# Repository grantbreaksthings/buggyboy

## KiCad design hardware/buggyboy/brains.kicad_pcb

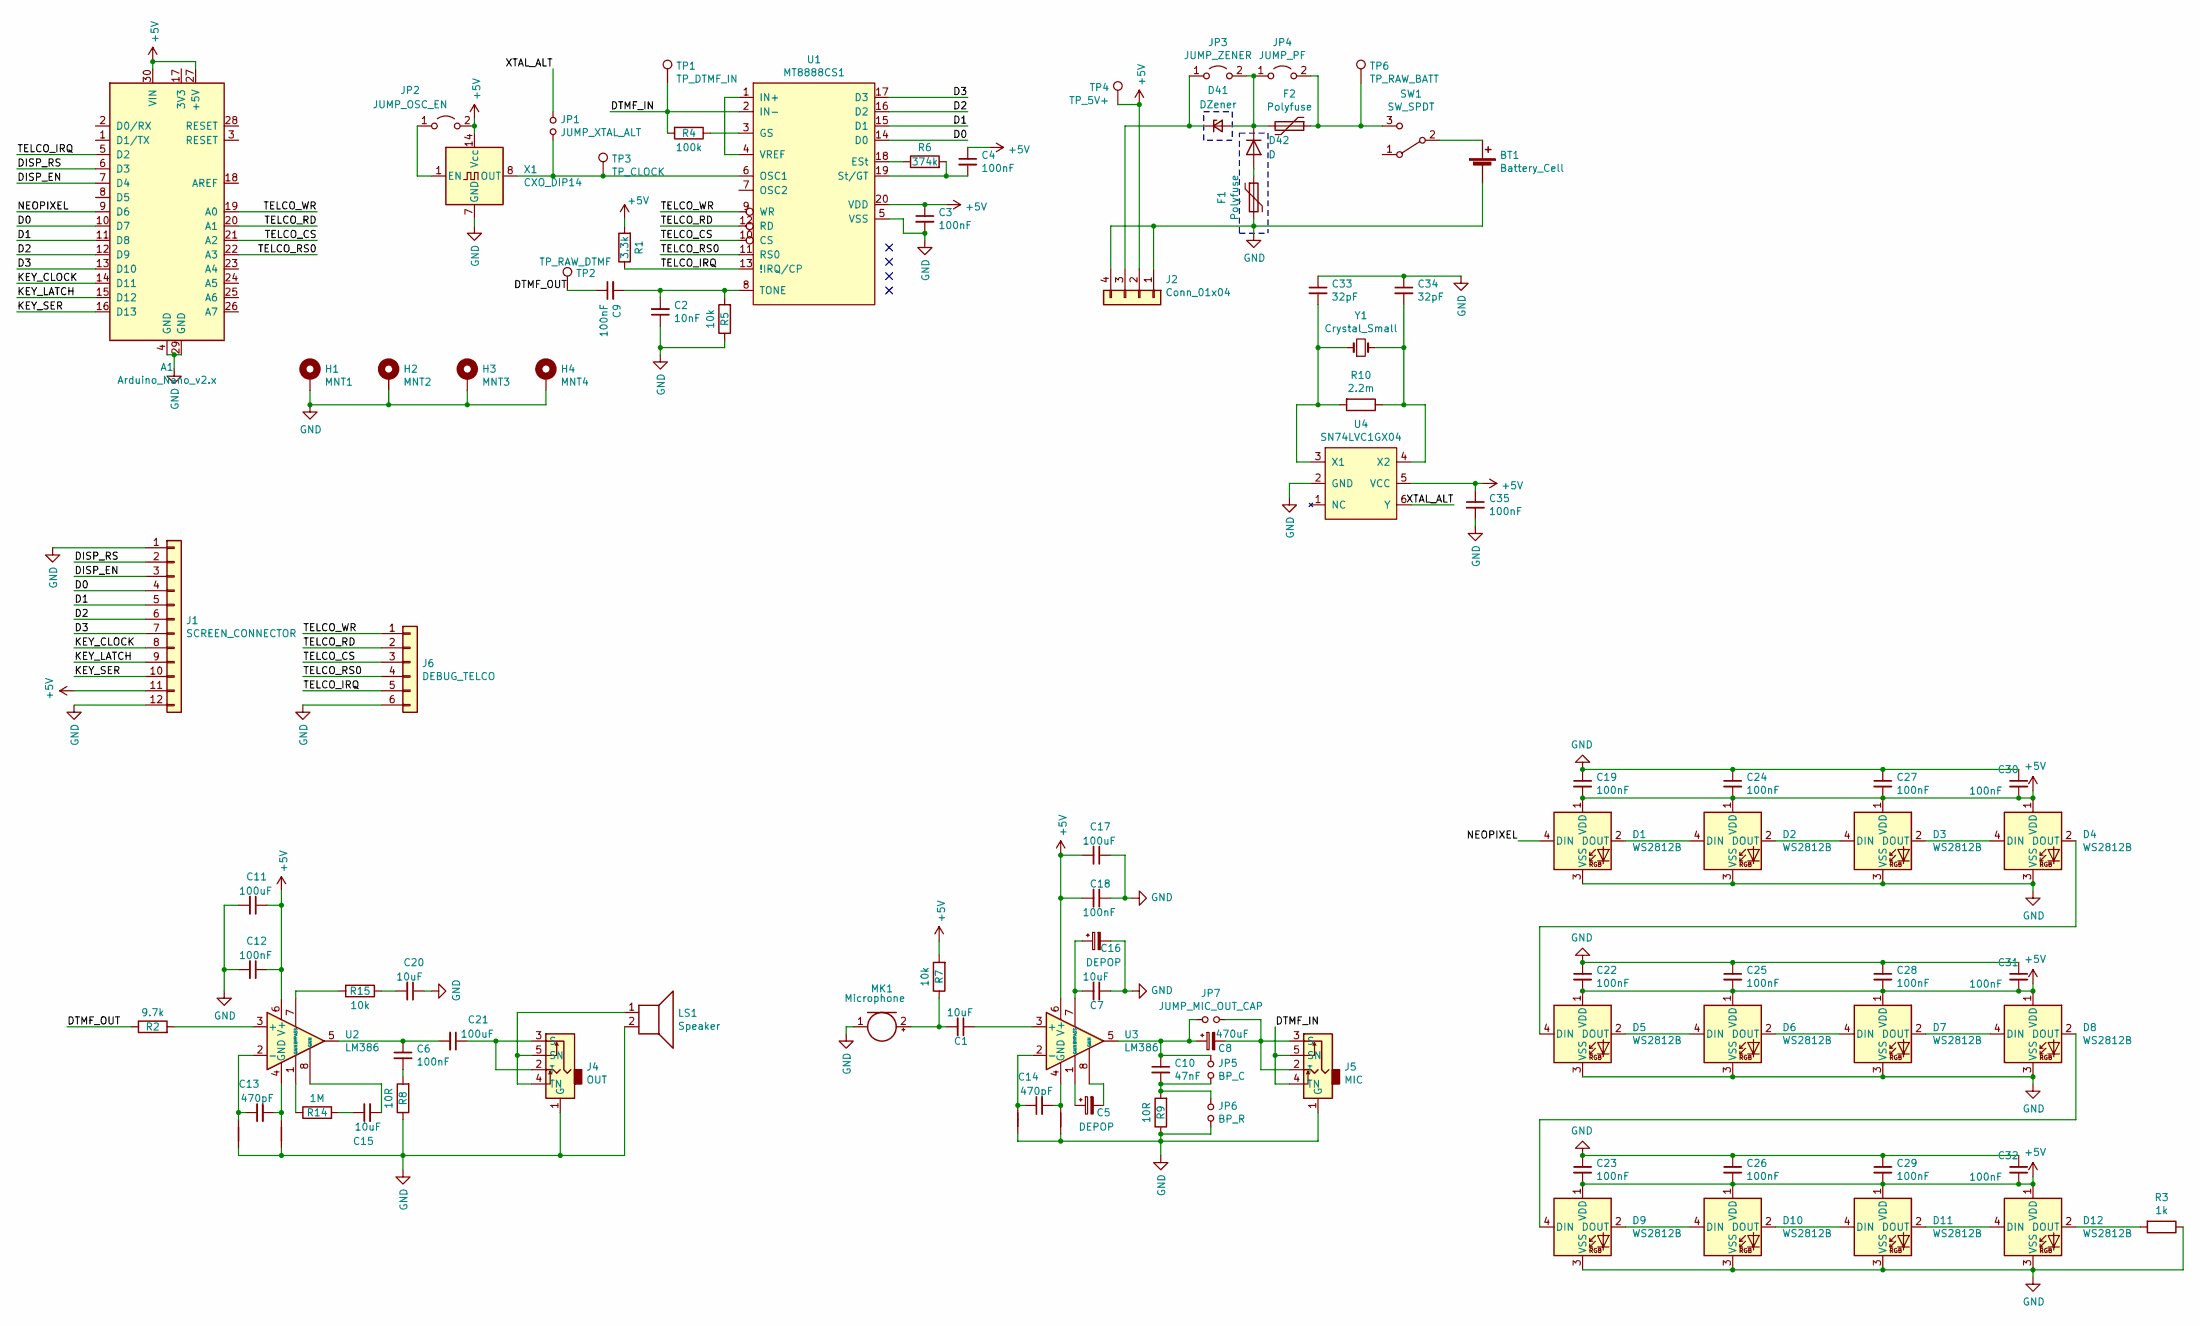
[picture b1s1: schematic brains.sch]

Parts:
A1: Arduino_Nano_v2.x; Arduino_Nano
BT1: Battery_Cell; BatteryHolder_BC2AAPC
C1, C7, C15, C20: 10uF; C_0805_2012Metric_Pad1.18x1.45mm_HandSolder
C2: 10nF; C_0805_2012Metric_Pad1.18x1.45mm_HandSolder
C3, C4, C6, C9, C12, C18, C19, C22, C23, C24, C25, C26, C27, C28, C29, C30, C31, C32, C35: 100nF; C_0603_1608Metric_Pad1.08x0.95mm_HandSolder
C5, C16: DEPOP; CP_Radial_D8.0mm_P3.80mm
C8: 470uF; CP_Radial_D8.0mm_P3.80mm
C10: 47nF; C_0603_1608Metric_Pad1.08x0.95mm_HandSolder
C11, C17, C21: 100uF; C_1206_3216Metric_Pad1.33x1.80mm_HandSolder
C13, C14: 470pF; C_0805_2012Metric_Pad1.18x1.45mm_HandSolder
C33, C34: 32pF; C_0402_1005Metric_Pad0.74x0.62mm_HandSolder
D1, D2, D3, D4, D5, D6, D7, D8, D9, D10, D11, D12: WS2812B; LED_WS2812B_PLCC4_5.0x5.0mm_P3.2mm
D41: DZener; D_SMB_Handsoldering
D42: D; D_SMA_Handsoldering
F1, F2: Polyfuse; Fuse_Littelfuse_395Series
H1: MNT1; MountingHole_4.3mm_M4_Pad_Via
H2: MNT2; MountingHole_4.3mm_M4_Pad_Via
H3: MNT3; MountingHole_4.3mm_M4_Pad_Via
H4: MNT4; MountingHole_4.3mm_M4_Pad_Via
J1: SCREEN_CONNECTOR; PinHeader_1x12_P2.54mm_Vertical
J2: Conn_01x04; MT3608_MODULE
J4: OUT; CUI_SJ1-3545N
J5: MIC; CUI_SJ1-3545N
J6: DEBUG_TELCO; PinHeader_1x06_P2.54mm_Vertical
JP1: JUMP_XTAL_ALT; SolderJumper-2_P1.3mm_Open_RoundedPad1.0x1.5mm
JP2: JUMP_OSC_EN; SolderJumper-2_P1.3mm_Open_RoundedPad1.0x1.5mm
JP3: JUMP_ZENER; SolderJumper-2_P1.3mm_Open_RoundedPad1.0x1.5mm
JP4: JUMP_PF; SolderJumper-2_P1.3mm_Open_RoundedPad1.0x1.5mm
JP5: BP_C; SolderJumper-2_P1.3mm_Open_RoundedPad1.0x1.5mm
JP6: BP_R; SolderJumper-2_P1.3mm_Open_RoundedPad1.0x1.5mm
JP7: JUMP_MIC_OUT_CAP; SolderJumper-2_P1.3mm_Open_RoundedPad1.0x1.5mm
LS1: Speaker; PinSocket_1x02_P2.54mm_Vertical
MK1: Microphone; PinSocket_1x02_P2.54mm_Vertical
NT1, NT2, NT3, NT4: Net-Tie_2; NetTie-2_SMD_Pad0.5mm
R1: 3.3k; R_0805_2012Metric_Pad1.20x1.40mm_HandSolder
R2: 9.7k; R_0805_2012Metric_Pad1.20x1.40mm_HandSolder
R3: 1k; R_0805_2012Metric_Pad1.20x1.40mm_HandSolder
R4: 100k; R_0805_2012Metric_Pad1.20x1.40mm_HandSolder
R5, R7, R15: 10k; R_0805_2012Metric_Pad1.20x1.40mm_HandSolder
R6: 374k; R_0805_2012Metric_Pad1.20x1.40mm_HandSolder
R8, R9: 10R; R_0805_2012Metric_Pad1.20x1.40mm_HandSolder
R10: 2.2m; R_0805_2012Metric_Pad1.20x1.40mm_HandSolder
R14: 1M; R_0805_2012Metric_Pad1.20x1.40mm_HandSolder
SW1: SW_SPDT; SW_E-Switch_EG1224_SPDT_Angled
TP1: TP_DTMF_IN; TestPoint_Pad_D2.5mm
TP2: TP_RAW_DTMF; TestPoint_Pad_D2.5mm
TP3: TP_CLOCK; TestPoint_Pad_D2.5mm
TP4: TP_5V+; TestPoint_Pad_D2.5mm
TP6: TP_RAW_BATT; TestPoint_Pad_D2.5mm
U1: MT8888CS1; SOIC-20W_7.5x12.8mm_P1.27mm
U2, U3: LM386; DIP-8_W7.62mm_LongPads
U4: SN74LVC1GX04; SOT-563
X1: CXO_DIP14; Oscillator_DIP-14
Y1: Crystal_Small; Crystal_HC49-U_Vertical

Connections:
+5V: A1.27 (+5V), A1.30 (VIN), C3.1, C4.1, C11.1, C12.1, C17.2, C18.2, C19.2, C22.2, C23.2, C24.2, C25.2, C26.2, C27.2, C28.2, C29.2, C30.2, C31.2, C32.2, C35.1, D1.1 (VDD), D2.1 (VDD), D3.1 (VDD), D4.1 (VDD), D5.1 (VDD), D6.1 (VDD), D7.1 (VDD), D8.1 (VDD), D9.1 (VDD), D10.1 (VDD), D11.1 (VDD), D12.1 (VDD), J1.11, J2.2, JP2.2 (B), R1.2, R7.2, TP4.1, U1.20 (VDD), U2.6 (V+), U3.6 (V+), U4.5 (VCC), X1.14 (Vcc)
/D0: A1.10 (D7), J1.4, U1.14 (D0)
/D1: A1.11 (D8), J1.5, U1.15 (D1)
/D2: A1.12 (D9), J1.6, U1.16 (D2)
/D3: A1.13 (D10), J1.7, U1.17 (D3)
/DISP_EN: A1.7 (D4), J1.3
/DISP_RS: A1.6 (D3), J1.2
/DTMF_IN: J5.4 (TN), J5.5 (SN), R4.2, TP1.1, U1.2 (IN-)
/DTMF_OUT: C9.1, R2.1, TP2.1
/KEY_CLOCK: A1.14 (D11), J1.8
/KEY_LATCH: A1.15 (D12), J1.9
/KEY_SER: A1.16 (D13), J1.10
/NEOPIXEL: A1.9 (D6), D1.4 (DIN)
/TELCO_CS: A1.21 (A2), J6.3, U1.10 (CS)
/TELCO_IRQ: A1.5 (D2), J6.5, R1.1, U1.13 (!IRQ/CP)
/TELCO_RD: A1.20 (A1), J6.2, U1.12 (RD)
/TELCO_RS0: A1.22 (A3), J6.4, U1.11 (RS0)
/TELCO_WR: A1.19 (A0), J6.1, U1.9 (WR)
/XTAL_ALT: JP1.1, U4.6 (Y)
GND: A1.4 (GND), A1.29 (GND), BT1.2 (-), C2.1, C3.2, C7.1, C11.2, C12.2, C16.2, C17.1, C18.1, C19.1, C20.1, C22.1, C23.1, C24.1, C25.1, C26.1, C27.1, C28.1, C29.1, C30.1, C31.1, C32.1, C33.1, C34.1, C35.2, D1.3 (VSS), D2.3 (VSS), D3.3 (VSS), D4.3 (VSS), D5.3 (VSS), D6.3 (VSS), D7.3 (VSS), D8.3 (VSS), D9.3 (VSS), D10.3 (VSS), D11.3 (VSS), D12.3 (VSS), F1.2, H1.1, H2.1, H3.1, H4.1, J1.1, J1.12, J2.1, J2.4, J4.1 (G), J5.1 (G), J6.6, JP6.2, LS1.2, MK1.1 (-), NT1.2, NT2.2, NT3.2, NT4.2, R3.1, R5.1, R8.1, R9.1, U1.5 (VSS), U4.2 (GND), X1.7 (GND)
unnamed: BT1.1 (+), SW1.2 (B)
unnamed: C1.1, U3.3 (+)
unnamed: C1.2, MK1.2 (+), R7.1
unnamed: C2.2, C9.2, R5.2, U1.8 (TONE)
unnamed: C4.2, R6.2, U1.19 (St/GT)
unnamed: C5.1, U3.1 (GAIN)
unnamed: C5.2, U3.8 (GAIN)
unnamed: C6.2, R8.2
unnamed: C8.2, J5.2 (T), J5.3 (S), JP7.2
unnamed: C8.1, C10.1, JP5.1, JP7.1, U3.5
unnamed: C10.2, JP5.2, JP6.1, R9.2
unnamed: C13.1, NT1.1, U2.2 (-)
unnamed: C13.2, NT2.1, U2.4 (GND)
unnamed: C14.1, NT3.1, U3.2 (-)
unnamed: C14.2, NT4.1, U3.4 (GND)
unnamed: C15.1, R14.2
unnamed: C15.2, U2.8 (GAIN)
unnamed: C7.2, C16.1, U3.7 (BYPASS)
unnamed: C20.2, R15.1
unnamed: C21.1, J4.2 (T), J4.3 (S)
unnamed: C6.1, C21.2, U2.5
unnamed: C33.2, R10.2, U4.3 (X1), Y1.1
unnamed: C34.2, R10.1, U4.4 (X2), Y1.2
unnamed: D1.2 (DOUT), D2.4 (DIN)
unnamed: D2.2 (DOUT), D3.4 (DIN)
unnamed: D3.2 (DOUT), D4.4 (DIN)
unnamed: D4.2 (DOUT), D5.4 (DIN)
unnamed: D5.2 (DOUT), D6.4 (DIN)
unnamed: D6.2 (DOUT), D7.4 (DIN)
unnamed: D7.2 (DOUT), D8.4 (DIN)
unnamed: D8.2 (DOUT), D9.4 (DIN)
unnamed: D10.2 (DOUT), D11.4 (DIN)
unnamed: D9.2 (DOUT), D10.4 (DIN)
unnamed: D11.2 (DOUT), D12.4 (DIN)
unnamed: D12.2 (DOUT), R3.2
unnamed: D41.1 (K), J2.3, JP3.1 (A)
unnamed: D41.2 (A), D42.1 (K), F2.2, JP3.2 (B), JP4.1 (A)
unnamed: D42.2 (A), F1.1
unnamed: F2.1, JP4.2 (B), SW1.3 (C), TP6.1
unnamed: J4.4 (TN), J4.5 (SN), LS1.1
unnamed: JP1.2, TP3.1, U1.6 (OSC1), X1.8 (OUT)
unnamed: JP2.1 (A), X1.1 (EN)
unnamed: R2.2, U2.3 (+)
unnamed: R4.1, U1.3 (GS)
unnamed: R6.1, U1.18 (ESt)
unnamed: R14.1, U2.1 (GAIN)
unnamed: R15.2, U2.7 (BYPASS)
unnamed: U1.1 (IN+), U1.4 (VREF)

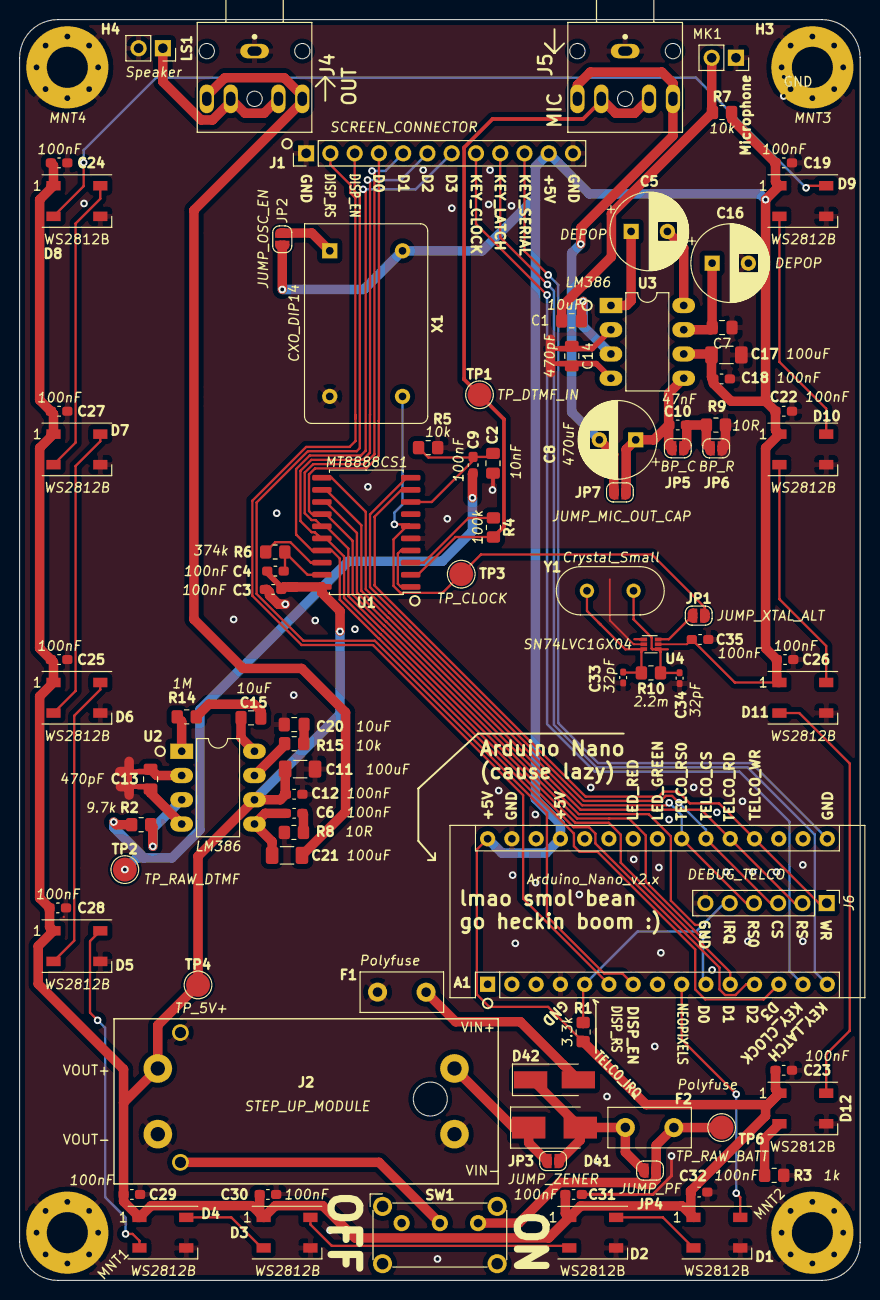
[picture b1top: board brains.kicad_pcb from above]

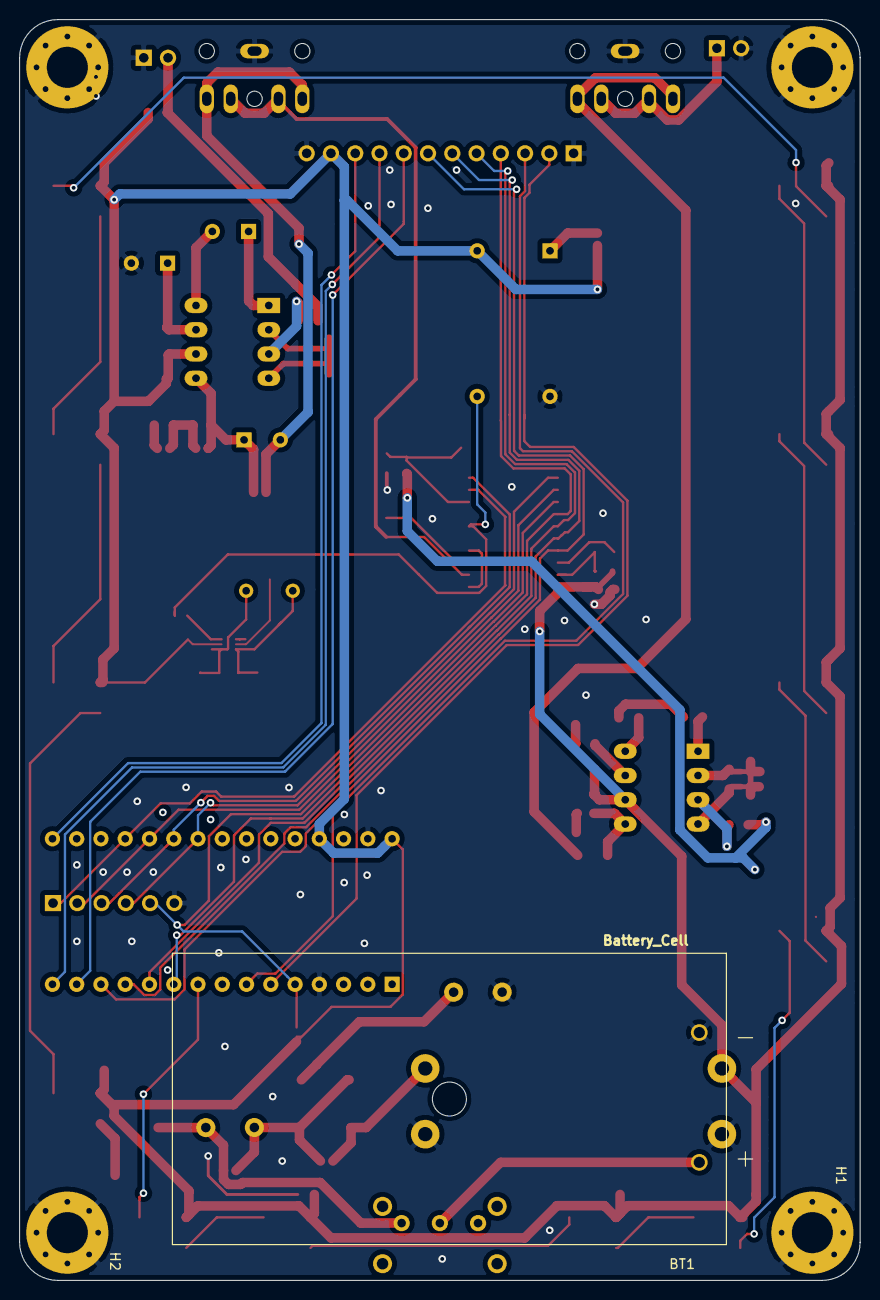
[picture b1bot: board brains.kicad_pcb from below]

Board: 2 copper layers, 88.0 x 132.0 mm, 99 parts (3 on the bottom side), 68 nets.

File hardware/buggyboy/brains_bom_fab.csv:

Designator,Package,Quantity,Designation,LCSC Part Number
"C22,C3,C4,C6,C9,C12,C18,C19,C23,C24,C25,C26,C27,C28,C29,C30,C31,C32,C35",C_0603_1608Metric_Pad1.08x0.95mm_HandSolder,19,100nF,C14663
"D9,D2,D6,D10,D3,D7,D11,D4,D8,D12,D1,D5",LED_WS2812B_PLCC4_5.0x5.0mm_P3.2mm,12,WS2812B,C2761795
"C1,C15,C20, C7",C_0805_2012Metric_Pad1.18x1.45mm_HandSolder,3,10uF,C15850
C10,C_0603_1608Metric_Pad1.08x0.95mm_HandSolder,1,47nF,C1622
"C11,C17,C21",C_1206_3216Metric_Pad1.33x1.80mm_HandSolder,3,100uF,C15008
"C13,C14",C_0805_2012Metric_Pad1.18x1.45mm_HandSolder,2,470pF,C1743
D42,D_SMA_Handsoldering,1,D,C95872
R1,R_0805_2012Metric_Pad1.20x1.40mm_HandSolder,1,3.3k,C26010
R2,R_0805_2012Metric_Pad1.20x1.40mm_HandSolder,1,9.7k,C17414
R4,R_0805_2012Metric_Pad1.20x1.40mm_HandSolder,1,100k,C149504
"R5,R7,R15",R_0805_2012Metric_Pad1.20x1.40mm_HandSolder,3,10k,C17414
R6,R_0805_2012Metric_Pad1.20x1.40mm_HandSolder,1,374k,C17649
"R8,R9",R_0805_2012Metric_Pad1.20x1.40mm_HandSolder,2,10R,C17415
R14,R_0805_2012Metric_Pad1.20x1.40mm_HandSolder,1,1M,C17514
R3,R_0805_2012Metric_Pad1.20x1.40mm_HandSolder,1,1k,C17513
"C33,C34",C_0402_Metric_Pad1.08x0.95mm_HandSolder,2,32pF,C1570
R10,R_0805_2012Metric_Pad1.20x1.40mm_HandSolder,1,2.2m,C26113

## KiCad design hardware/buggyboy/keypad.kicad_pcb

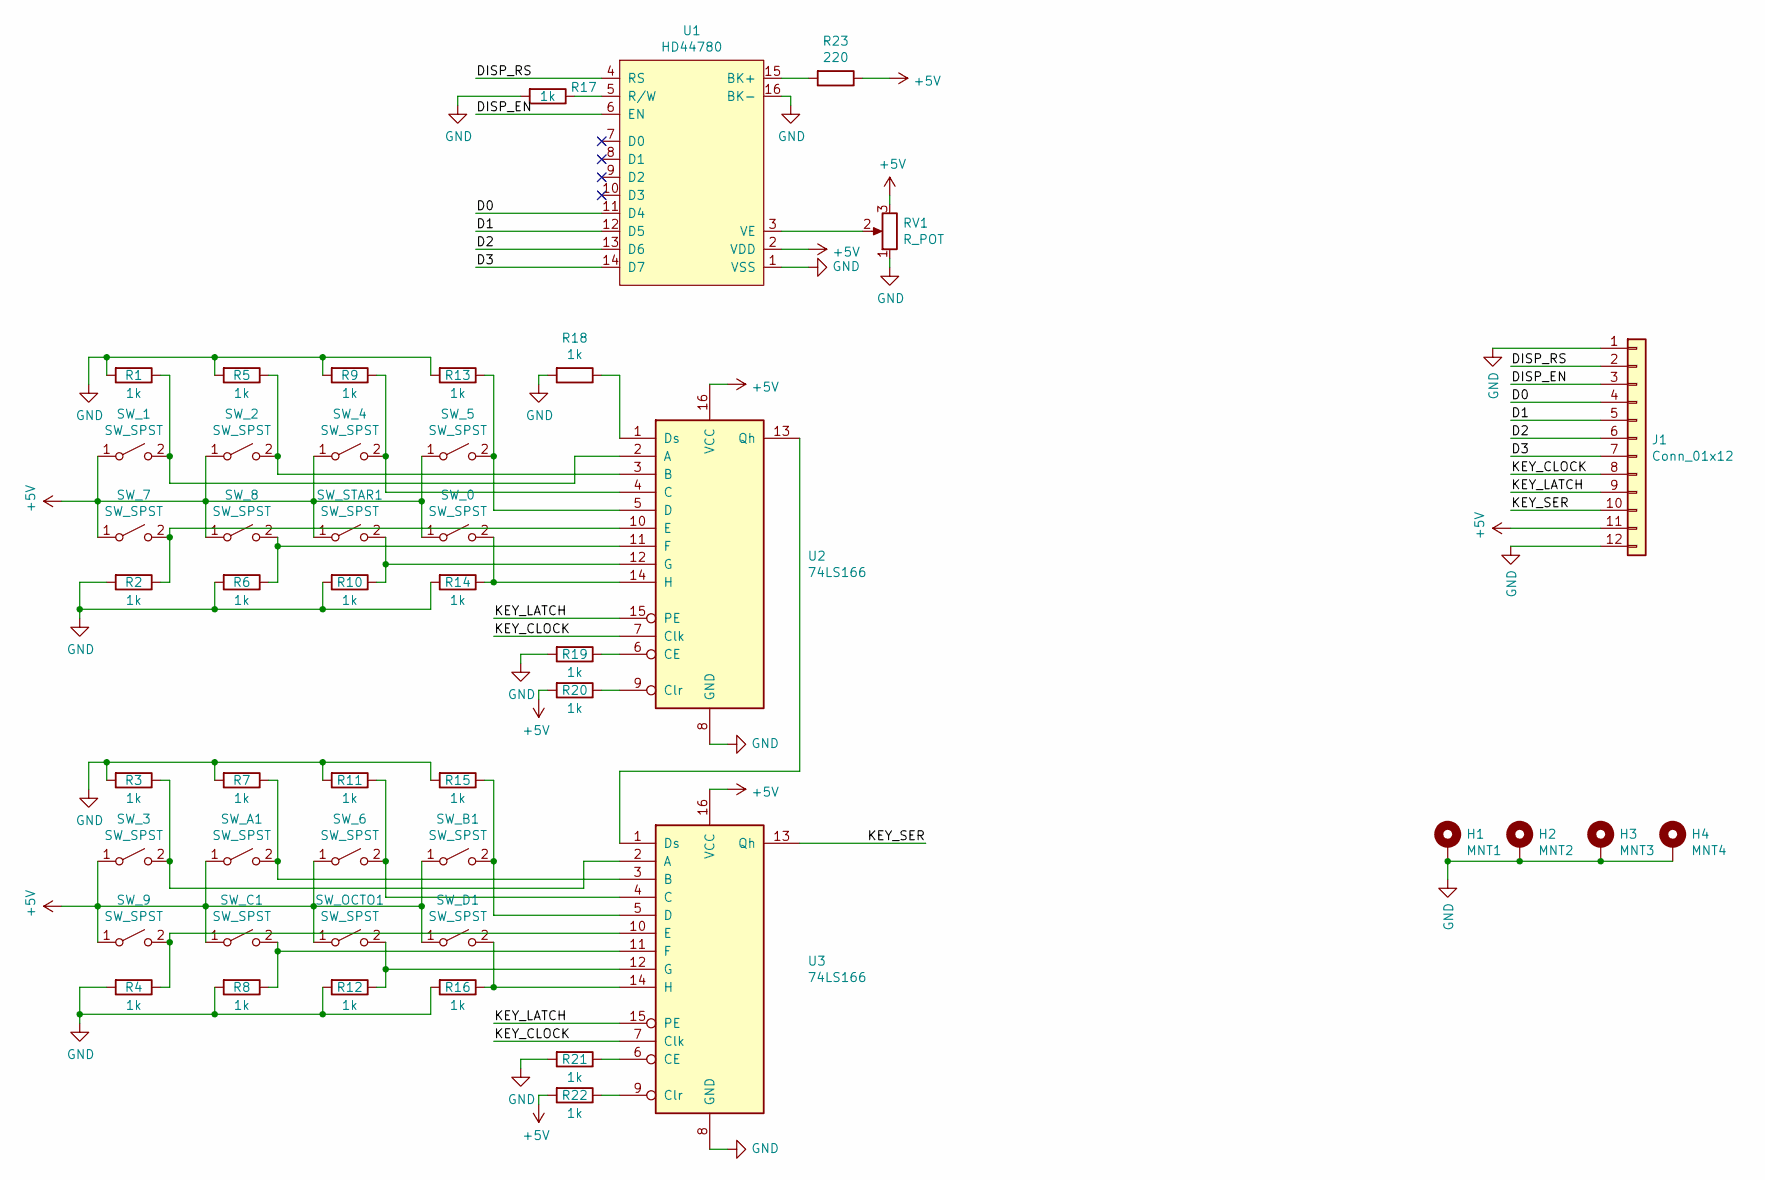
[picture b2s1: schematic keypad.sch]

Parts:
H1: MNT1; MountingHole_4.3mm_M4_Pad_Via
H2: MNT2; MountingHole_4.3mm_M4_Pad_Via
H3: MNT3; MountingHole_4.3mm_M4_Pad_Via
H4: MNT4; MountingHole_4.3mm_M4_Pad_Via
J1: Conn_01x12; PinHeader_1x12_P2.54mm_Vertical
R1, R2, R3, R4, R5, R6, R7, R8, R9, R10, R11, R12, R13, R14, R15, R16, R17, R18, R19, R20, R21, R22: 1k; R_0603_1608Metric_Pad0.98x0.95mm_HandSolder
R23: 220; R_0603_1608Metric_Pad0.98x0.95mm_HandSolder
RV1: R_POT; TRIM_3313J-1-103E
SW_0, SW_1, SW_2, SW_3, SW_4, SW_5, SW_6, SW_7, SW_8, SW_9: SW_SPST; SW_Cherry_MX_1.00u_PCB
SW_A1: SW_SPST; SW_Cherry_MX_1.00u_PCB
SW_B1: SW_SPST; SW_Cherry_MX_1.00u_PCB
SW_C1: SW_SPST; SW_Cherry_MX_1.00u_PCB
SW_D1: SW_SPST; SW_Cherry_MX_1.00u_PCB
SW_OCTO1: SW_SPST; SW_Cherry_MX_1.00u_PCB
SW_STAR1: SW_SPST; SW_Cherry_MX_1.00u_PCB
U1: HD44780; WC1602A
U2, U3: 74LS166; DIP-16_W7.62mm_LongPads

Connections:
+5V: J1.11, R20.2, R22.2, R23.1, RV1.3, SW_0.1 (A), SW_1.1 (A), SW_2.1 (A), SW_3.1 (A), SW_4.1 (A), SW_5.1 (A), SW_6.1 (A), SW_7.1 (A), SW_8.1 (A), SW_9.1 (A), SW_A1.1 (A), SW_B1.1 (A), SW_C1.1 (A), SW_D1.1 (A), SW_OCTO1.1 (A), SW_STAR1.1 (A), U1.2 (VDD), U2.16 (VCC), U3.16 (VCC)
/D0: J1.4, U1.11 (D4)
/D1: J1.5, U1.12 (D5)
/D2: J1.6, U1.13 (D6)
/D3: J1.7, U1.14 (D7)
/DISP_EN: J1.3, U1.6 (EN)
/DISP_RS: J1.2, U1.4 (RS)
/KEY_CLOCK: J1.8, U2.7 (Clk), U3.7 (Clk)
/KEY_LATCH: J1.9, U2.15 (PE), U3.15 (PE)
/KEY_SER: J1.10, U3.13 (Qh)
GND: H1.1, H2.1, H3.1, H4.1, J1.1, J1.12, R1.2, R2.2, R3.2, R4.2, R5.2, R6.2, R7.2, R8.2, R9.2, R10.2, R11.2, R12.2, R13.2, R14.2, R15.2, R16.2, R17.2, R18.2, R19.2, R21.2, RV1.1, U1.1 (VSS), U1.16 (BK-), U2.8 (GND), U3.8 (GND)
unnamed: R1.1, SW_1.2 (B), U2.2 (A)
unnamed: R2.1, SW_7.2 (B), U2.10 (E)
unnamed: R3.1, SW_3.2 (B), U3.2 (A)
unnamed: R4.1, SW_9.2 (B), U3.10 (E)
unnamed: R5.1, SW_2.2 (B), U2.3 (B)
unnamed: R6.1, SW_8.2 (B), U2.11 (F)
unnamed: R7.1, SW_A1.2 (B), U3.3 (B)
unnamed: R8.1, SW_C1.2 (B), U3.11 (F)
unnamed: R9.1, SW_4.2 (B), U2.4 (C)
unnamed: R10.1, SW_STAR1.2 (B), U2.12 (G)
unnamed: R11.1, SW_6.2 (B), U3.4 (C)
unnamed: R12.1, SW_OCTO1.2 (B), U3.12 (G)
unnamed: R13.1, SW_5.2 (B), U2.5 (D)
unnamed: R14.1, SW_0.2 (B), U2.14 (H)
unnamed: R15.1, SW_B1.2 (B), U3.5 (D)
unnamed: R16.1, SW_D1.2 (B), U3.14 (H)
unnamed: R17.1, U1.5 (R/W)
unnamed: R18.1, U2.1 (Ds)
unnamed: R19.1, U2.6 (CE)
unnamed: R20.1, U2.9 (Clr)
unnamed: R21.1, U3.6 (CE)
unnamed: R22.1, U3.9 (Clr)
unnamed: R23.2, U1.15 (BK+)
unnamed: RV1.2, U1.3 (VE)
unnamed: U2.13 (Qh), U3.1 (Ds)

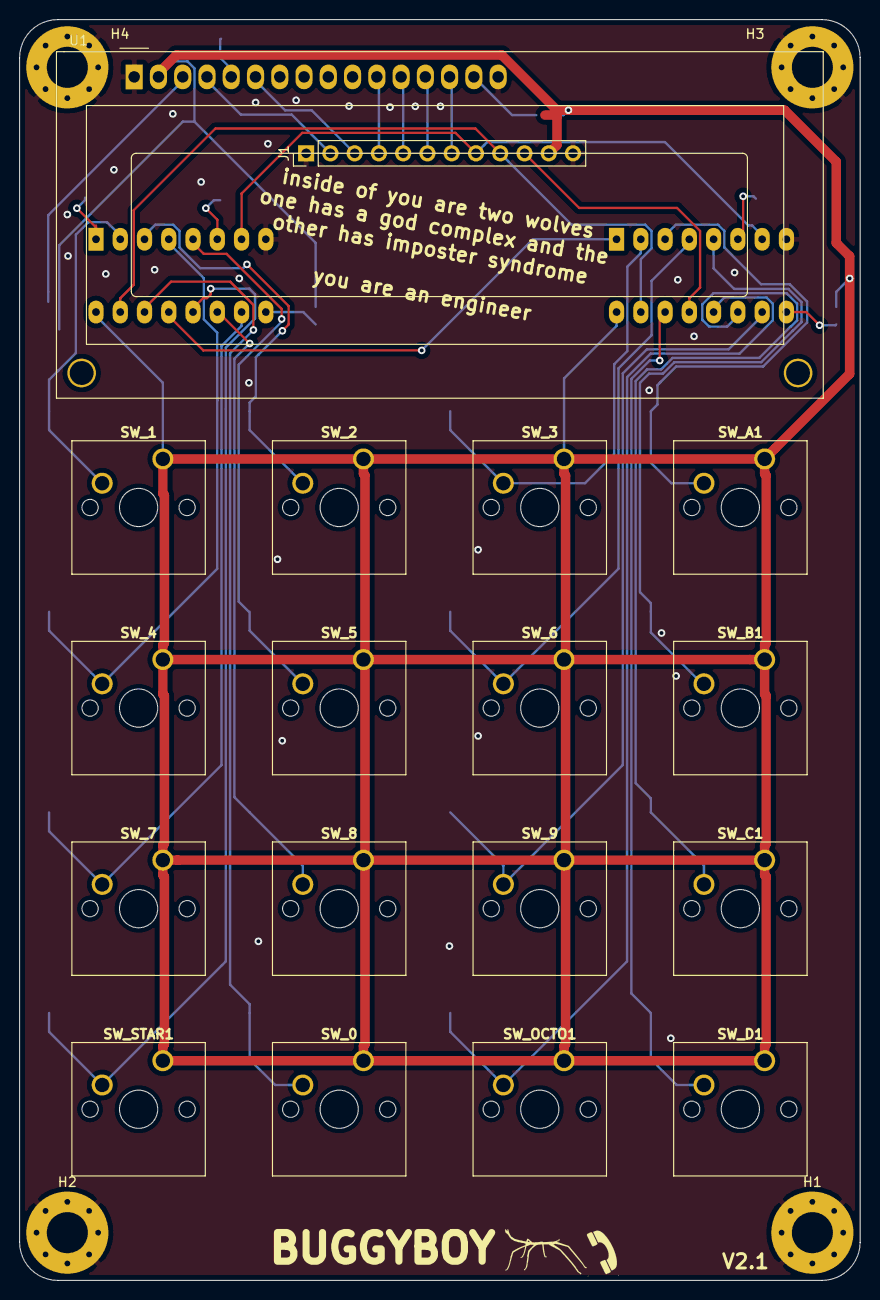
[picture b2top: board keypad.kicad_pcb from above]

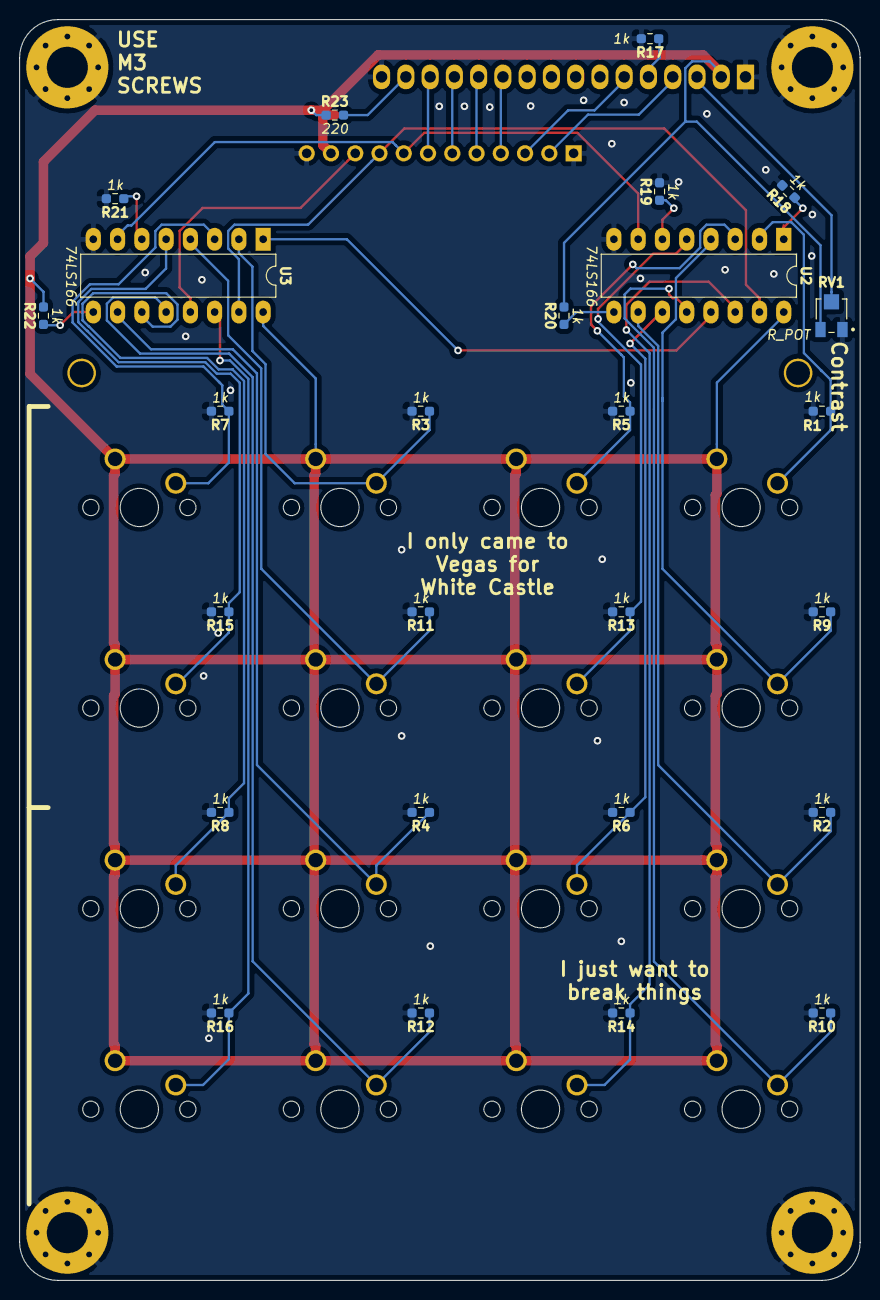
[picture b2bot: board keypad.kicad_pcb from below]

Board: 2 copper layers, 88.0 x 132.0 mm, 48 parts (26 on the bottom side), 36 nets.

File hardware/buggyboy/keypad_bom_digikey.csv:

"Id";"Designator";"Package";"Quantity";"Designation";"Supplier and ref";
1;"J1";"PinHeader_1x12_P2.54mm_Vertical";1;"Conn_01x12";;;
2;"RV1";"TRIM_3313J-1-103E";1;"R_POT";;;
3;"H1";"MountingHole_4.3mm_M4_Pad_Via";1;"MNT1";;;
4;"H2";"MountingHole_4.3mm_M4_Pad_Via";1;"MNT2";;;
5;"U2,U3";"DIP-16_W7.62mm_LongPads";2;"74LS166";;;
6;"G***";"pone";1;"LOGO";;;
7;"G***";"nugg";1;"LOGO";;;
8;"H3";"MountingHole_4.3mm_M4_Pad_Via";1;"MNT3";;;
9;"H4";"MountingHole_4.3mm_M4_Pad_Via";1;"MNT4";;;
10;"R1,R2,R3,R4,R5,R6,R7,R8,R9,R10,R11,R12,R13,R14,R15,R16,R17,R18,R19,R20,R21,R22";"R_0603_1608Metric_Pad0.98x0.95mm_HandSolder";22;"1k";;;
11;"R23";"R_0603_1608Metric_Pad0.98x0.95mm_HandSolder";1;"220";;;
12;"SW_0,SW_1,SW_2,SW_3,SW_4,SW_5,SW_6,SW_7,SW_8,SW_9,SW_A1,SW_B1,SW_C1,SW_D1,SW_OCTO1,SW_STAR1";"SW_Cherry_MX_1.00u_PCB";16;"SW_SPST";;;
13;"U1";"WC1602A";1;"HD44780";;;

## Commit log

2022-05-31 before redoin
2022-05-31 routed again
2022-06-12 ordering
